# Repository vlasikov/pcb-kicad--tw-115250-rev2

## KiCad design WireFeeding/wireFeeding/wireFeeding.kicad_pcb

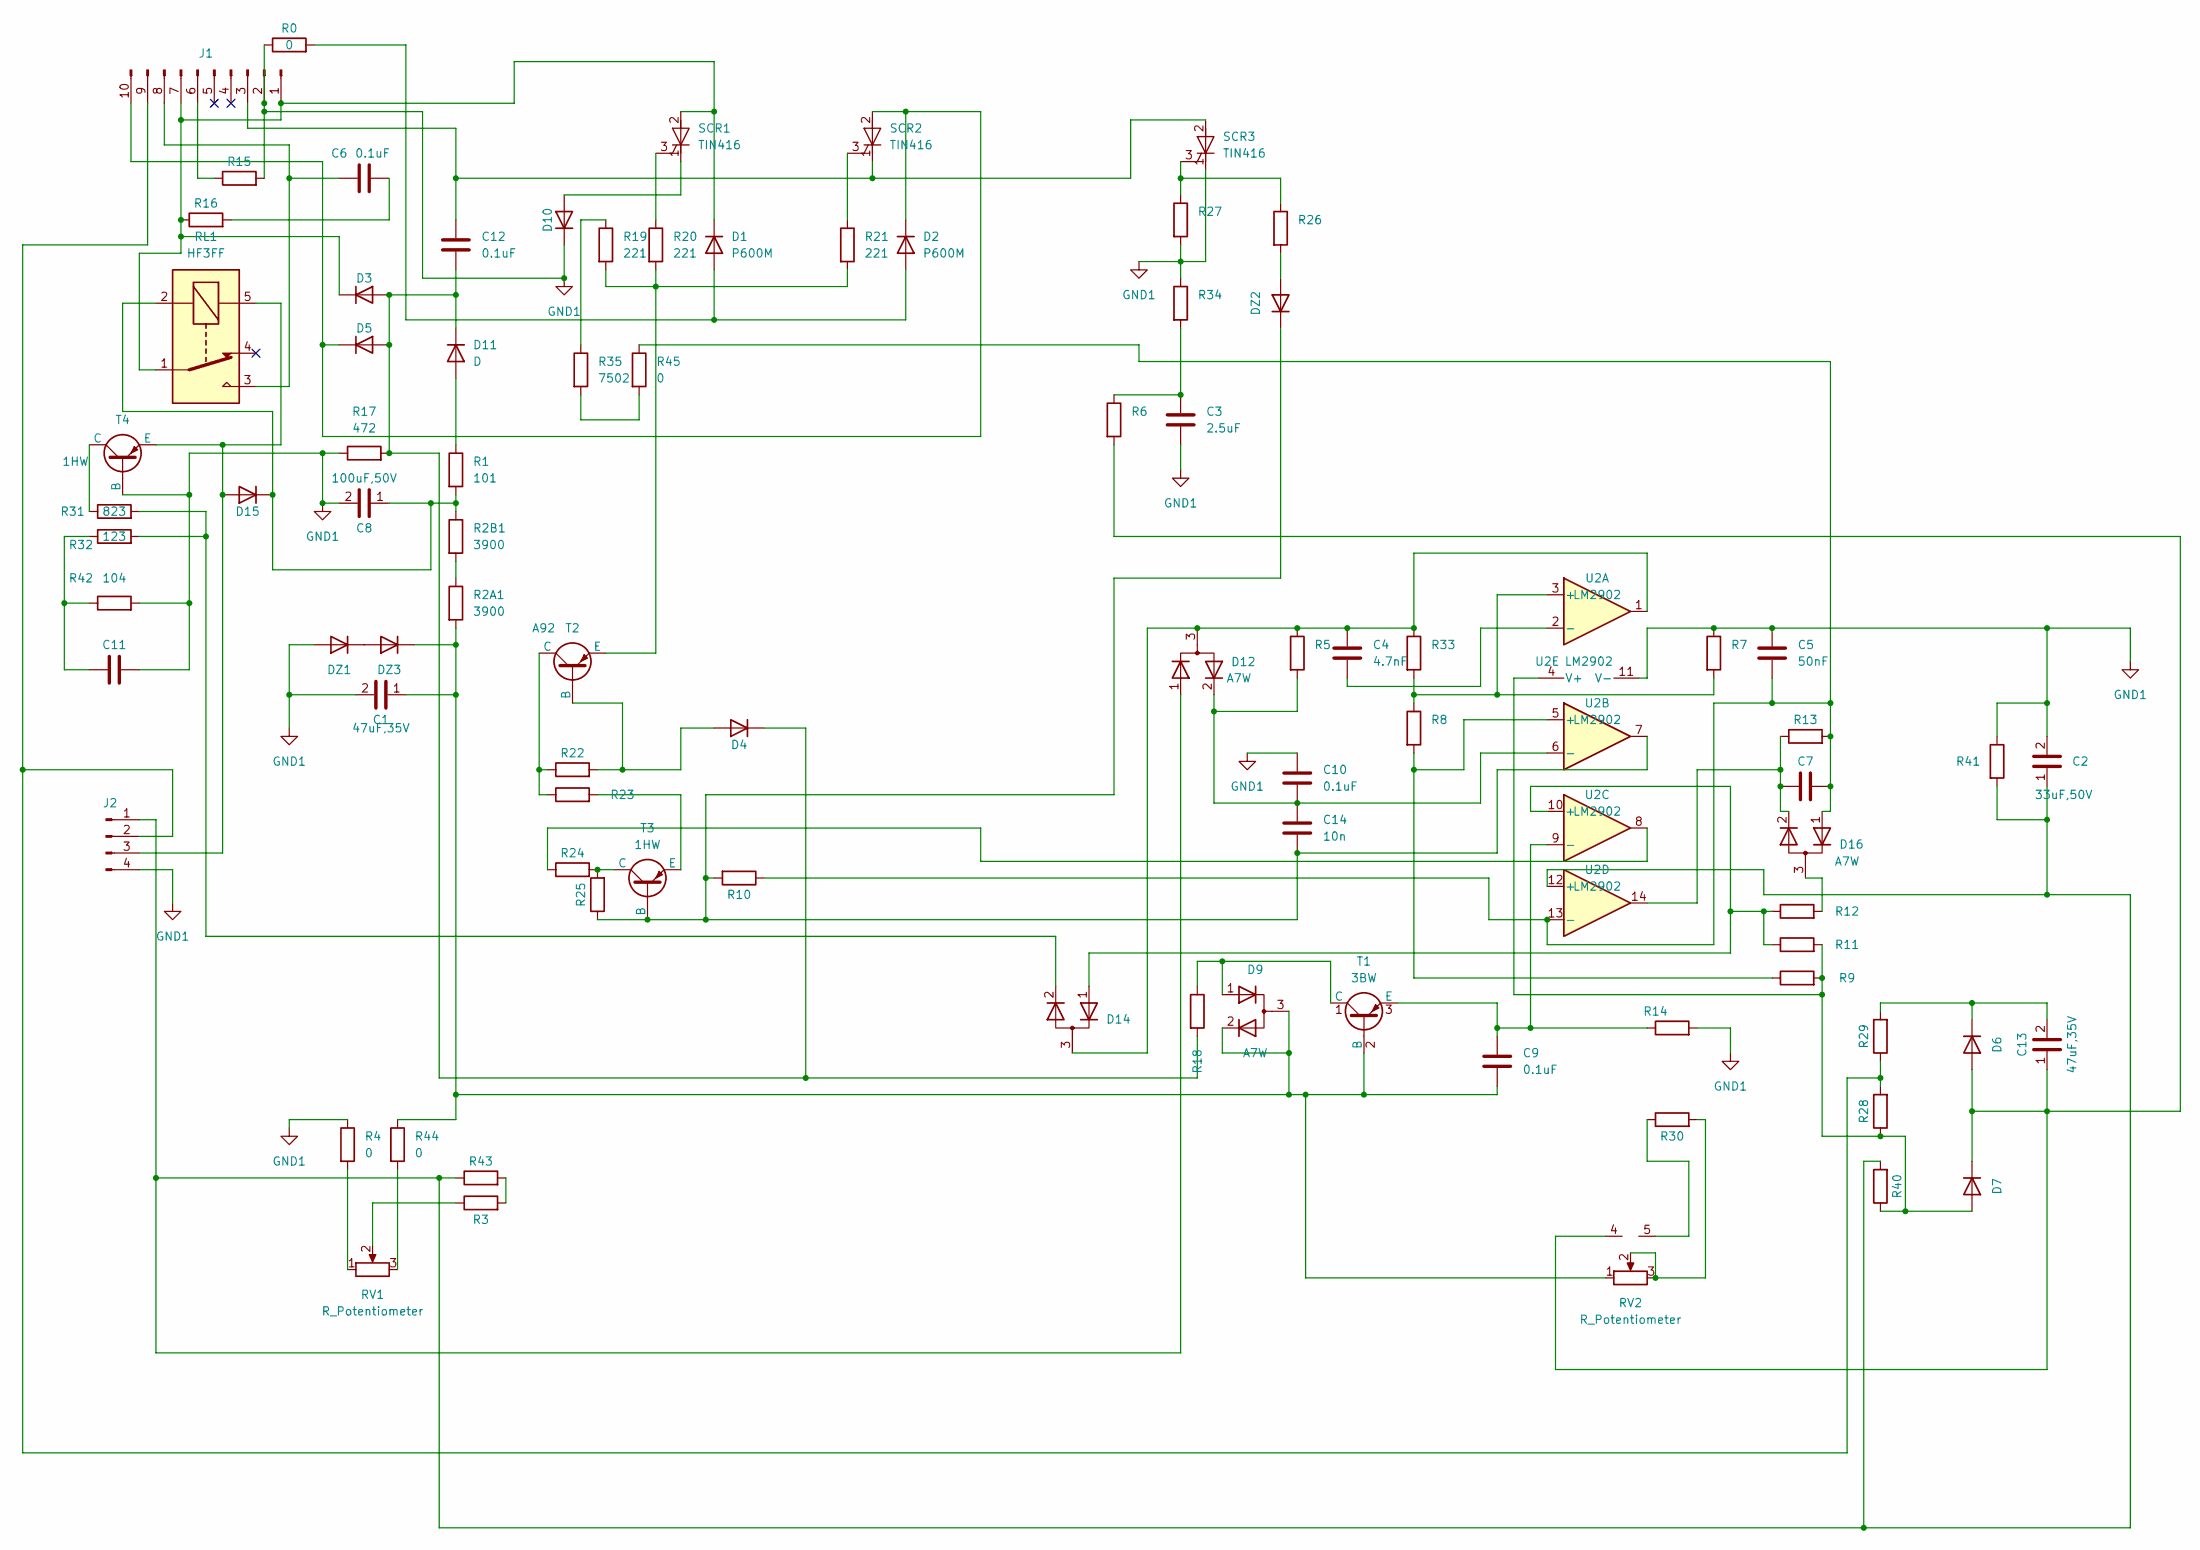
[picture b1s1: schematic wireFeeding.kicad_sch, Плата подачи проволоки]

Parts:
C1, C13: 47uF,35V; CP_Elec_6.3x5.4
C2: 33uF,50V; CP_Elec_8x10.5
C3: 2.5uF; C_1206_3216Metric
C4: 4.7nF; C_0603_1608Metric
C5: 50nF; C_0603_1608Metric
C6, C12: 0.1uF; C_Rect_L11.0mm_W2.8mm_P10.00mm_MKT
C7: 1.1uF; C_1206_3216Metric
C8: 100uF,50V; CP_Elec_8x10.5
C9, C10: 0.1uF; C_0603_1608Metric
C11: 1uF; C_1206_3216Metric
C14: 10n; C_0603_1608Metric
D1, D2: P600M; D_DO-201AD_P15.24mm_Horizontal
D3, D4, D5, D6, D7, D10, D11, D15: D; D_2512_6332Metric
D9, D12, D14, D16: A7W; SOT-23
DZ1, DZ2, DZ3: BZV55C6V2; D_2512_6332Metric
J1: Conn_01x10_Pin; Molex_KK-396_5273-10A_1x10_P3.96mm_Vertical
J2: Conn_01x04_Pin; PinHeader_1x04_P2.54mm_Vertical
R0: 0; R_2512_6332Metric
R1, R26: 101; R_2512_6332Metric
R2A1, R2B1: 3900; R_2512_6332Metric
R3, R12, R32: 123; R_0603_1608Metric
R4, R44, R45: 0; R_0603_1608Metric
R5, R11: 1803; R_0603_1608Metric
R6: 105; R_0603_1608Metric
R7, R28: 152; R_0603_1608Metric
R8: 474; R_0603_1608Metric
R9: 155; R_0603_1608Metric
R10: 103; R_0603_1608Metric
R13: 564; R_0603_1608Metric
R14, R31: 823; R_0603_1608Metric
R15: 220; R_0805_2012Metric
R16: 022; R_0805_2012Metric
R17, R23: 472; R_2512_6332Metric
R18, R22: 682; R_0603_1608Metric
R19, R20, R21, R27: 221; R_0805_2012Metric
R24: 333; R_0603_1608Metric
R25: 332; R_0603_1608Metric
R29: 220; R_0603_1608Metric
R30: 822; R_0603_1608Metric
R33: 475; R_0603_1608Metric
R34: 222; R_0603_1608Metric
R35: 7502; R_0603_1608Metric
R40: 2403; R_0603_1608Metric
R41: 153; R_0603_1608Metric
R42: 104; R_0603_1608Metric
R43: 223; R_0603_1608Metric
RL1: HF3FF; Relay_SPDT_Omron-G5LE-1
RV1: R_Potentiometer; Potentiometer_Alps_RK163_Single_Horizontal
RV2: R_Potentiometer; Potentiometer_Alps_RK163_Dual_Horizontal
SCR1, SCR2, SCR3: TIN416; TO-220-3_Vertical
T1: 3BW; SOT-23
T2: A92; SOT-23
T3, T4: 1HW; SOT-23
U2: LM2902; SO-14_3.9x8.65mm_P1.27mm

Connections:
GND1: C1.2, C2.2, C3.2, C5.1, C8.2, C10.1, C11.2, D10.1 (K), DZ1.2 (A), J1.2, J2.4, R0.1, R4.1, R7.1, R14.2, R15.2, R17.1, R27.2, R34.1, R41.1, R42.2, SCR3.1 (K), T4.2 (B), U2.11 (V-)
unnamed: C3.1, R6.1, R34.2
unnamed: C6.2, R16.2
unnamed: C7.2, D16.2 (K), R13.1, U2.14
unnamed: C11.1, R32.1, R42.1
unnamed: D1.2 (A), D2.2 (A), R0.2
unnamed: D1.1 (K), D3.1 (K), J1.1, J1.7, R16.1, RL1.1, SCR1.2 (A)
unnamed: D2.1 (K), D5.1 (K), J1.10, SCR2.2 (A)
unnamed: D4.2 (A), R22.2, T2.2 (B)
unnamed: C13.1, D6.2 (A), D7.1 (K), R6.2, RV2.4
unnamed: C13.2, D6.1 (K), R29.2
unnamed: D7.2 (A), R9.2, R11.2, R28.1, R40.1, U2.4 (V+)
unnamed: C1.1, C9.2, D9.2 (K), D9.3 (A), DZ3.1 (K), R2A1.2, R44.1, RV2.1, T1.2 (B)
unnamed: D10.2 (A), SCR1.1 (K)
unnamed: D11.2 (A), R1.1
unnamed: C12.2, D3.2 (A), D4.1 (K), D5.2 (A), D11.1 (K), R17.2, R18.2
unnamed: C4.1, D12.3 (A), D14.3 (A), R5.1, R33.1, U2.1
unnamed: D14.2 (K), R31.2, R32.2
unnamed: D15.2 (A), J2.3, RL1.5, T4.3 (E)
unnamed: C8.1, D15.1 (K), R1.2, R2B1.1, RL1.2
unnamed: D16.3 (A), R12.2
unnamed: DZ1.1 (K), DZ3.2 (A)
unnamed: DZ2.2 (A), R26.2
unnamed: C14.2, DZ2.1 (K), R10.2, R25.1, T3.2 (B), U2.7
unnamed: C12.1, J1.3, SCR2.1 (K), SCR3.2 (A)
unnamed: J1.6, R15.1
unnamed: C6.1, J1.8, RL1.3
unnamed: J1.9, J2.2, R28.2, R29.1
unnamed: C2.1, D12.1 (K), J2.1, R40.2, R41.2, R43.1, U2.12 (+)
unnamed: R2A1.1, R2B1.2
unnamed: R3.1, RV1.2
unnamed: R3.2, R43.2
unnamed: R4.2, RV1.1
unnamed: R19.1, R35.1
unnamed: R24.1, U2.8
unnamed: R30.1, RV2.5
unnamed: R30.2, RV2.2, RV2.3
unnamed: R35.2, R45.2
unnamed: R44.2, RV1.3
unnamed: R20.1, SCR1.3 (G)
unnamed: R21.1, SCR2.3 (G)
unnamed: R26.1, R27.1, SCR3.3 (G)
unnamed: D9.1 (K), R18.1, T1.1 (C)
unnamed: C9.1, R14.1, T1.3 (E), U2.9 (-)
unnamed: R22.1, R23.1, T2.1 (C)
unnamed: R19.2, R20.2, R21.2, T2.3 (E)
unnamed: R24.2, R25.2, T3.1 (C)
unnamed: R23.2, T3.3 (E)
unnamed: R31.1, T4.1 (C)
unnamed: R7.2, R8.1, R33.2, U2.3 (+)
unnamed: C4.2, U2.2 (-)
unnamed: R8.2, R9.1, U2.5 (+)
unnamed: C10.2, C14.1, D12.2 (K), R5.2, U2.6 (-)
unnamed: D14.1 (K), R11.1, R12.1, U2.10 (+)
unnamed: C5.2, C7.1, D16.1 (K), R10.1, R13.2, R45.1, U2.13 (-)

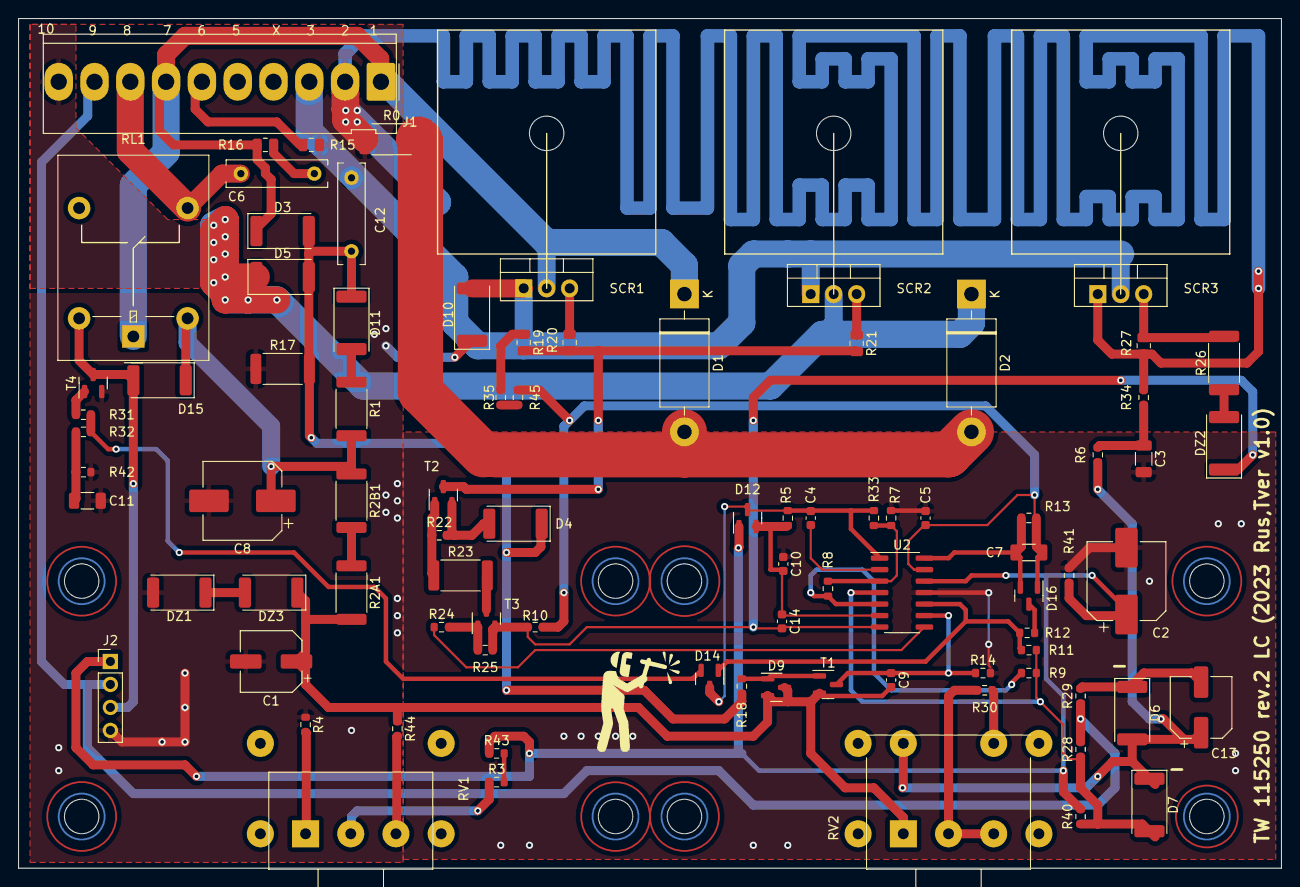
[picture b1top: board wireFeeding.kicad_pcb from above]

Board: 2 copper layers, 139.7 x 94.0 mm, 87 parts (0 on the bottom side), 55 nets.

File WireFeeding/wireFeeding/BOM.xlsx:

Designation | Frame | Qty | Value
C1,C13 | CP_Elec_6.3x5.4 | 2 | 47uF,35V
C10,C9 | C_0603_1608Metric | 2 | 0.1uF
C11 | C_1206_3216Metric | 1 | 1uF
C12,C6 | C_Rect_L11.0mm_W2.8mm_P10.00mm_MKT | 2 | 0.1uF
C14 | C_0603_1608Metric | 1 | 10n
C2 | CP_Elec_8x10.5 | 1 | 33uF,50V
C3 | C_1206_3216Metric | 1 | 2.5uF
C4 | C_0603_1608Metric | 1 | 4.7nF
C5 | C_0603_1608Metric | 1 | 50nF
C7 | C_1206_3216Metric | 1 | 1.1uF
C8 | CP_Elec_8x10.5 | 1 | 100uF,50V
D12,D9,D16,D14 | SOT-23 | 4 | A7W
D2,D1 | D_DO-201AD_P15.24mm_Horizontal | 2 | P600M
D7,D3,D4,D5,D15, D11,D6,D10 | D_2512_6332Metric | 8 | D
DZ3,DZ2,DZ1 | D_2512_6332Metric | 3 | BZV55C6V2
J1 | Molex_KK-396_5273-10A_1x10_P3.96mm_Vertical | 1 | Conn_01x10_Pin
J2 | PinHeader_1x04_P2.54mm_Vertical | 1 | Conn_01x04_Pin
R0 | R_2512_6332Metric | 1 | 0
R1,R26 | R_2512_6332Metric | 2 | 101
R10 | R_0603_1608Metric | 1 | 103
R13 | R_0603_1608Metric | 1 | 564
R15 | R_0805_2012Metric | 1 | 220
R16 | R_0805_2012Metric | 1 | 22
R18,R22 | R_0603_1608Metric | 2 | 682
R23,R17 | R_2512_6332Metric | 2 | 472
R24 | R_0603_1608Metric | 1 | 333
R25 | R_0603_1608Metric | 1 | 332
R27,R19,R21,R20 | R_0805_2012Metric | 4 | 221
R29 | R_0603_1608Metric | 1 | 220
R2A1,R2B1 | R_2512_6332Metric | 2 | 3900
R30 | R_0603_1608Metric | 1 | 822
R31,R14 | R_0603_1608Metric | 2 | 823
R32,R3,R12 | R_0603_1608Metric | 3 | 123
R33 | R_0603_1608Metric | 1 | 475
R34 | R_0603_1608Metric | 1 | 222
R35 | R_0603_1608Metric | 1 | 7502
R40 | R_0603_1608Metric | 1 | 2403
R41 | R_0603_1608Metric | 1 | 153
R42 | R_0603_1608Metric | 1 | 104
R43 | R_0603_1608Metric | 1 | 223
R45,R44,R4 | R_0603_1608Metric | 3 | 0
R5,R11 | R_0603_1608Metric | 2 | 1803
R6 | R_0603_1608Metric | 1 | 105
R7,R28 | R_0603_1608Metric | 2 | 152
R8 | R_0603_1608Metric | 1 | 474
R9 | R_0603_1608Metric | 1 | 155
RL1 | Relay_SPDT_Omron-G5LE-1 | 1 | HF3FF
RV1 | Potentiometer_Alps_RK163_Single_Horizontal | 1 | R_Potentiometer
RV2 | Potentiometer_Alps_RK163_Dual_Horizontal | 1 | R_Potentiometer
SCR2,SCR3,SCR1 | TO-220-3_Vertical | 3 | TIN416
T1 | SOT-23 | 1 | 3BW
T2 | SOT-23 | 1 | A92
T4,T3 | SOT-23 | 2 | 1HW
U2 | SO-14_3.9x8.65mm_P1.27mm | 1 | LM2902
